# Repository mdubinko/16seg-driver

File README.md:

# 16seg-driver

Driving a 16-segment display with shift registers, as documented on the YouTube channel Think Like Tesla.

Requires an external microcontroller driving lines for data, clock, and latch, as well as even/odd for multiplexing.

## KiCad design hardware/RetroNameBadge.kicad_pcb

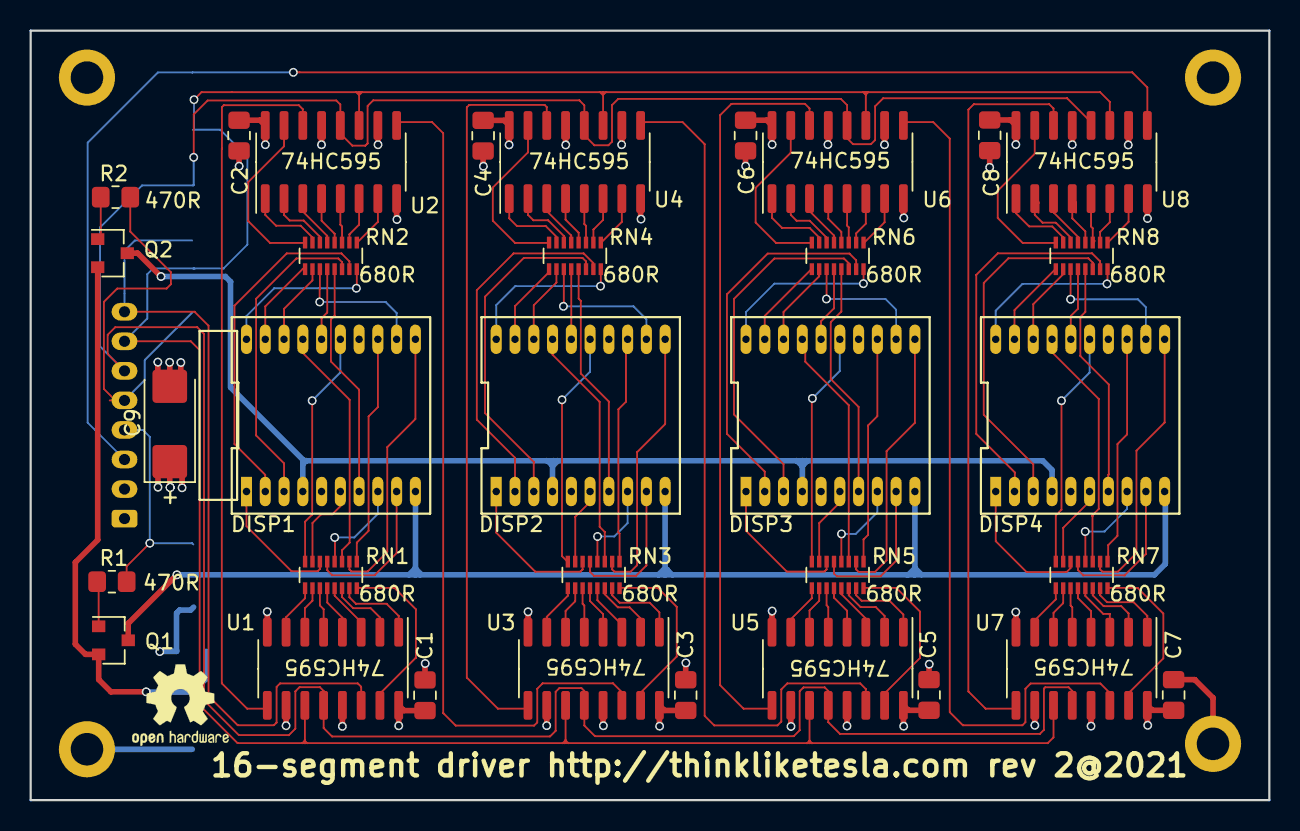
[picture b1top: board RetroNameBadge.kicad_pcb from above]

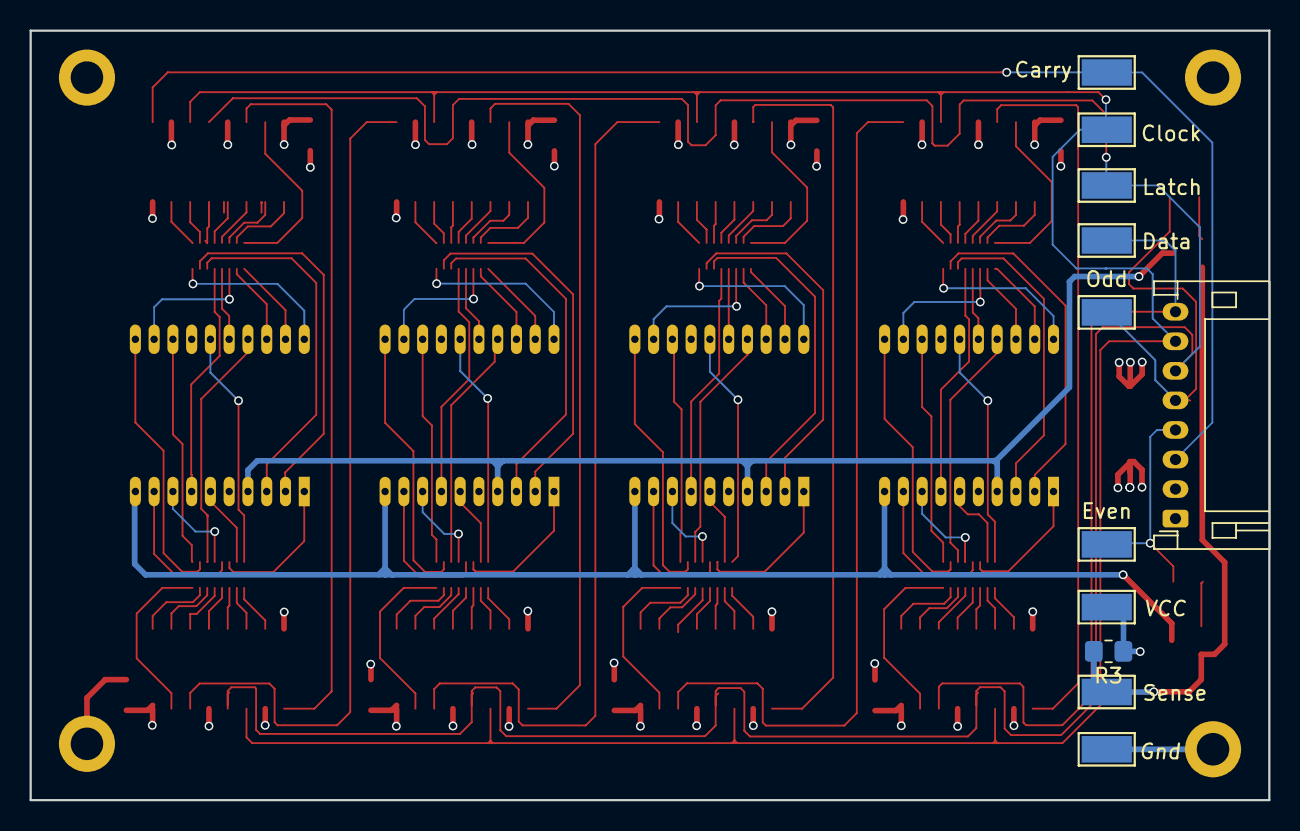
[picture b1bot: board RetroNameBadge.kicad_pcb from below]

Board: 4 copper layers, 83.8 x 52.1 mm, 44 parts (11 on the bottom side), 148 nets.

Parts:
C1, C2, C3, C4, C5, C6, C7, C8: 100n; C_0805_2012Metric_Pad1.18x1.45mm_HandSolder
C9: 10u Tantalum; CP_EIA-6032-28_Kemet-C_Pad2.25x2.35mm_HandSolder
DISP1, DISP2, DISP3, DISP4: 16SEGMENTx2CHAR; DIP-20_405_ELL
J1: Conn_8pin; JST_PH_S8B-PH-K_1x08_P2.00mm_Horizontal
Q1, Q2: MMBT3906; SOT-23
R1, R2: 470R; R_0805_2012Metric_Pad1.20x1.40mm_HandSolder
R3: Unpopulated; R_0805_2012Metric_Pad1.20x1.40mm_HandSolder
RN1, RN2, RN3, RN4, RN5, RN6, RN7, RN8: 680R; R_Array_Convex_8x0602
TP1: Data; TestPoint_Keystone_5015_Micro-Minature
TP2: Clock; TestPoint_Keystone_5015_Micro-Minature
TP3: Latch; TestPoint_Keystone_5015_Micro-Minature
TP4: Carry; TestPoint_Keystone_5015_Micro-Minature
TP5: Odd; TestPoint_Keystone_5015_Micro-Minature
TP6: Even; TestPoint_Keystone_5015_Micro-Minature
TP7: VCC; TestPoint_Keystone_5015_Micro-Minature
TP8: Gnd; TestPoint_Keystone_5015_Micro-Minature
TP9: Sense; TestPoint_Keystone_5015_Micro-Minature
U1, U2, U3, U4, U5, U6, U7, U8: 74HC595; SOIC-16_3.9x9.9mm_P1.27mm

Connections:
/A1: DISP1.13, RN1.9
/A2: DISP2.13, RN3.9
/A3: DISP3.13, RN5.9
/A4: DISP4.13, RN7.9
/B1: DISP1.11, RN1.10
/B2: DISP2.11, RN3.10
/B3: DISP3.11, RN5.10
/B4: DISP4.11, RN7.10
/C1: DISP1.17, RN1.11
/C2: DISP2.17, RN3.11
/C3: DISP3.17, RN5.11
/C4: DISP4.17, RN7.11
/D1: DISP1.8, RN1.12
/D2: DISP2.8, RN3.12
/D3: DISP3.8, RN5.12
/D4: DISP4.8, RN7.12
/E1: DISP1.9, RN1.13
/E2: DISP2.9, RN3.13
/E3: DISP3.9, RN5.13
/E4: DISP4.9, RN7.13
/EA: DISP1.10, DISP2.10, DISP3.10, DISP4.10, Q1.3
/F1: DISP1.1, RN1.14
/F2: DISP2.1, RN3.14
/F3: DISP3.1, RN5.14
/F4: DISP4.1, RN7.14
/G1: DISP1.6, RN1.15
/G2: DISP2.6, RN3.15
/G3: DISP3.6, RN5.15
/G4: DISP4.6, RN7.15
/H1: DISP1.15, RN1.16
/H2: DISP2.15, RN3.16
/H3: DISP3.15, RN5.16
/H4: DISP4.15, RN7.16
/K1: DISP1.19, RN2.9
/K2: DISP2.19, RN4.9
/K3: DISP3.19, RN6.9
/K4: DISP4.19, RN8.9
/M1: DISP1.18, RN2.10
/M2: DISP2.18, RN4.10
/M3: DISP3.18, RN6.10
/M4: DISP4.18, RN8.10
/N1: DISP1.12, RN2.11
/N2: DISP2.12, RN4.11
/N3: DISP3.12, RN6.11
/N4: DISP4.12, RN8.11
/OA: DISP1.4, DISP2.4, DISP3.4, DISP4.4, Q2.3
/P1: DISP1.16, RN2.12
/P2: DISP2.16, RN4.12
/P3: DISP3.16, RN6.12
/P4: DISP4.16, RN8.12
/R1: DISP1.7, RN2.13
/R2: DISP2.7, RN4.13
/R3: DISP3.7, RN6.13
/R4: DISP4.7, RN8.13
/S1: DISP1.3, RN2.14
/S2: DISP2.3, RN4.14
/S3: DISP3.3, RN6.14
/S4: DISP4.3, RN8.14
/T1: DISP1.2, RN2.15
/T2: DISP2.2, RN4.15
/T3: DISP3.2, RN6.15
/T4: DISP4.2, RN8.15
/U1: DISP1.20, RN2.16
/U2: DISP2.20, RN4.16
/U3: DISP3.20, RN6.16
/U4: DISP4.20, RN8.16
Carry: J1.3, TP4.1, U8.9
Clock: J1.7, TP2.1, U1.11, U2.11, U3.11, U4.11, U5.11, U6.11, U7.11, U8.11
Data: J1.8, TP1.1, U1.14
Even: J1.4, R1.2, TP6.1
GND: C1.1, C2.1, C3.1, C4.1, C5.1, C6.1, C7.1, C8.1, C9.2, J1.1, TP8.1, U1.8, U1.13, U2.8, U2.13, U3.8, U3.13, U4.8, U4.13, U5.8, U5.13, U6.8, U6.13, U7.8, U7.13, U8.8, U8.13
Latch: J1.6, TP3.1, U1.12, U2.12, U3.12, U4.12, U5.12, U6.12, U7.12, U8.12
unnamed: Q1.1, R1.1
unnamed: Q1.2, Q2.2, R3.2, TP9.1
unnamed: Q2.1, R2.1
unnamed: RN1.1, U1.7
unnamed: RN1.2, U1.6
unnamed: RN1.3, U1.5
unnamed: RN1.4, U1.4
unnamed: RN1.5, U1.3
unnamed: RN1.6, U1.2
unnamed: RN1.7, U1.1
unnamed: RN1.8, U1.15
unnamed: RN2.1, U2.7
unnamed: RN2.2, U2.6
unnamed: RN2.3, U2.5
unnamed: RN2.4, U2.4
unnamed: RN2.5, U2.3
unnamed: RN2.6, U2.2
unnamed: RN2.7, U2.1
unnamed: RN2.8, U2.15
unnamed: RN3.1, U3.7
unnamed: RN3.2, U3.6
unnamed: RN3.3, U3.5
unnamed: RN3.4, U3.4
unnamed: RN3.5, U3.3
unnamed: RN3.6, U3.2
unnamed: RN3.7, U3.1
unnamed: RN3.8, U3.15
unnamed: RN4.1, U4.7
unnamed: RN4.2, U4.6
unnamed: RN4.3, U4.5
unnamed: RN4.4, U4.4
unnamed: RN4.5, U4.3
unnamed: RN4.6, U4.2
unnamed: RN4.7, U4.1
unnamed: RN4.8, U4.15
unnamed: RN5.1, U5.7
unnamed: RN5.2, U5.6
unnamed: RN5.3, U5.5
unnamed: RN5.4, U5.4
unnamed: RN5.5, U5.3
unnamed: RN5.6, U5.2
unnamed: RN5.7, U5.1
unnamed: RN5.8, U5.15
unnamed: RN6.1, U6.7
unnamed: RN6.2, U6.6
unnamed: RN6.3, U6.5
unnamed: RN6.4, U6.4
unnamed: RN6.5, U6.3
unnamed: RN6.6, U6.2
unnamed: RN6.7, U6.1
unnamed: RN6.8, U6.15
unnamed: RN7.1, U7.7
unnamed: RN7.2, U7.6
unnamed: RN7.3, U7.5
unnamed: RN7.4, U7.4
unnamed: RN7.5, U7.3
unnamed: RN7.6, U7.2
unnamed: RN7.7, U7.1
unnamed: RN7.8, U7.15
unnamed: RN8.1, U8.7
unnamed: RN8.2, U8.6
unnamed: RN8.3, U8.5
unnamed: RN8.4, U8.4
unnamed: RN8.5, U8.3
unnamed: RN8.6, U8.2
unnamed: RN8.7, U8.1
unnamed: RN8.8, U8.15
unnamed: U1.9, U2.14
unnamed: U2.9, U3.14
unnamed: U3.9, U4.14
unnamed: U4.9, U5.14
unnamed: U5.9, U6.14
unnamed: U6.9, U7.14
unnamed: U7.9, U8.14
Odd: J1.5, R2.2, TP5.1
VCC: C1.2, C2.2, C3.2, C4.2, C5.2, C6.2, C7.2, C8.2, C9.1, J1.2, R3.1, TP7.1, U1.10, U1.16, U2.10, U2.16, U3.10, U3.16, U4.10, U4.16, U5.10, U5.16, U6.10, U6.16, U7.10, U7.16, U8.10, U8.16

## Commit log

2021-02-15 Revised hardware specs
2021-08-22 Final rev2 sent to production

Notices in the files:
parts and their libraries:
Copyright 2016 Accelerated Designs. All rights reserved.
